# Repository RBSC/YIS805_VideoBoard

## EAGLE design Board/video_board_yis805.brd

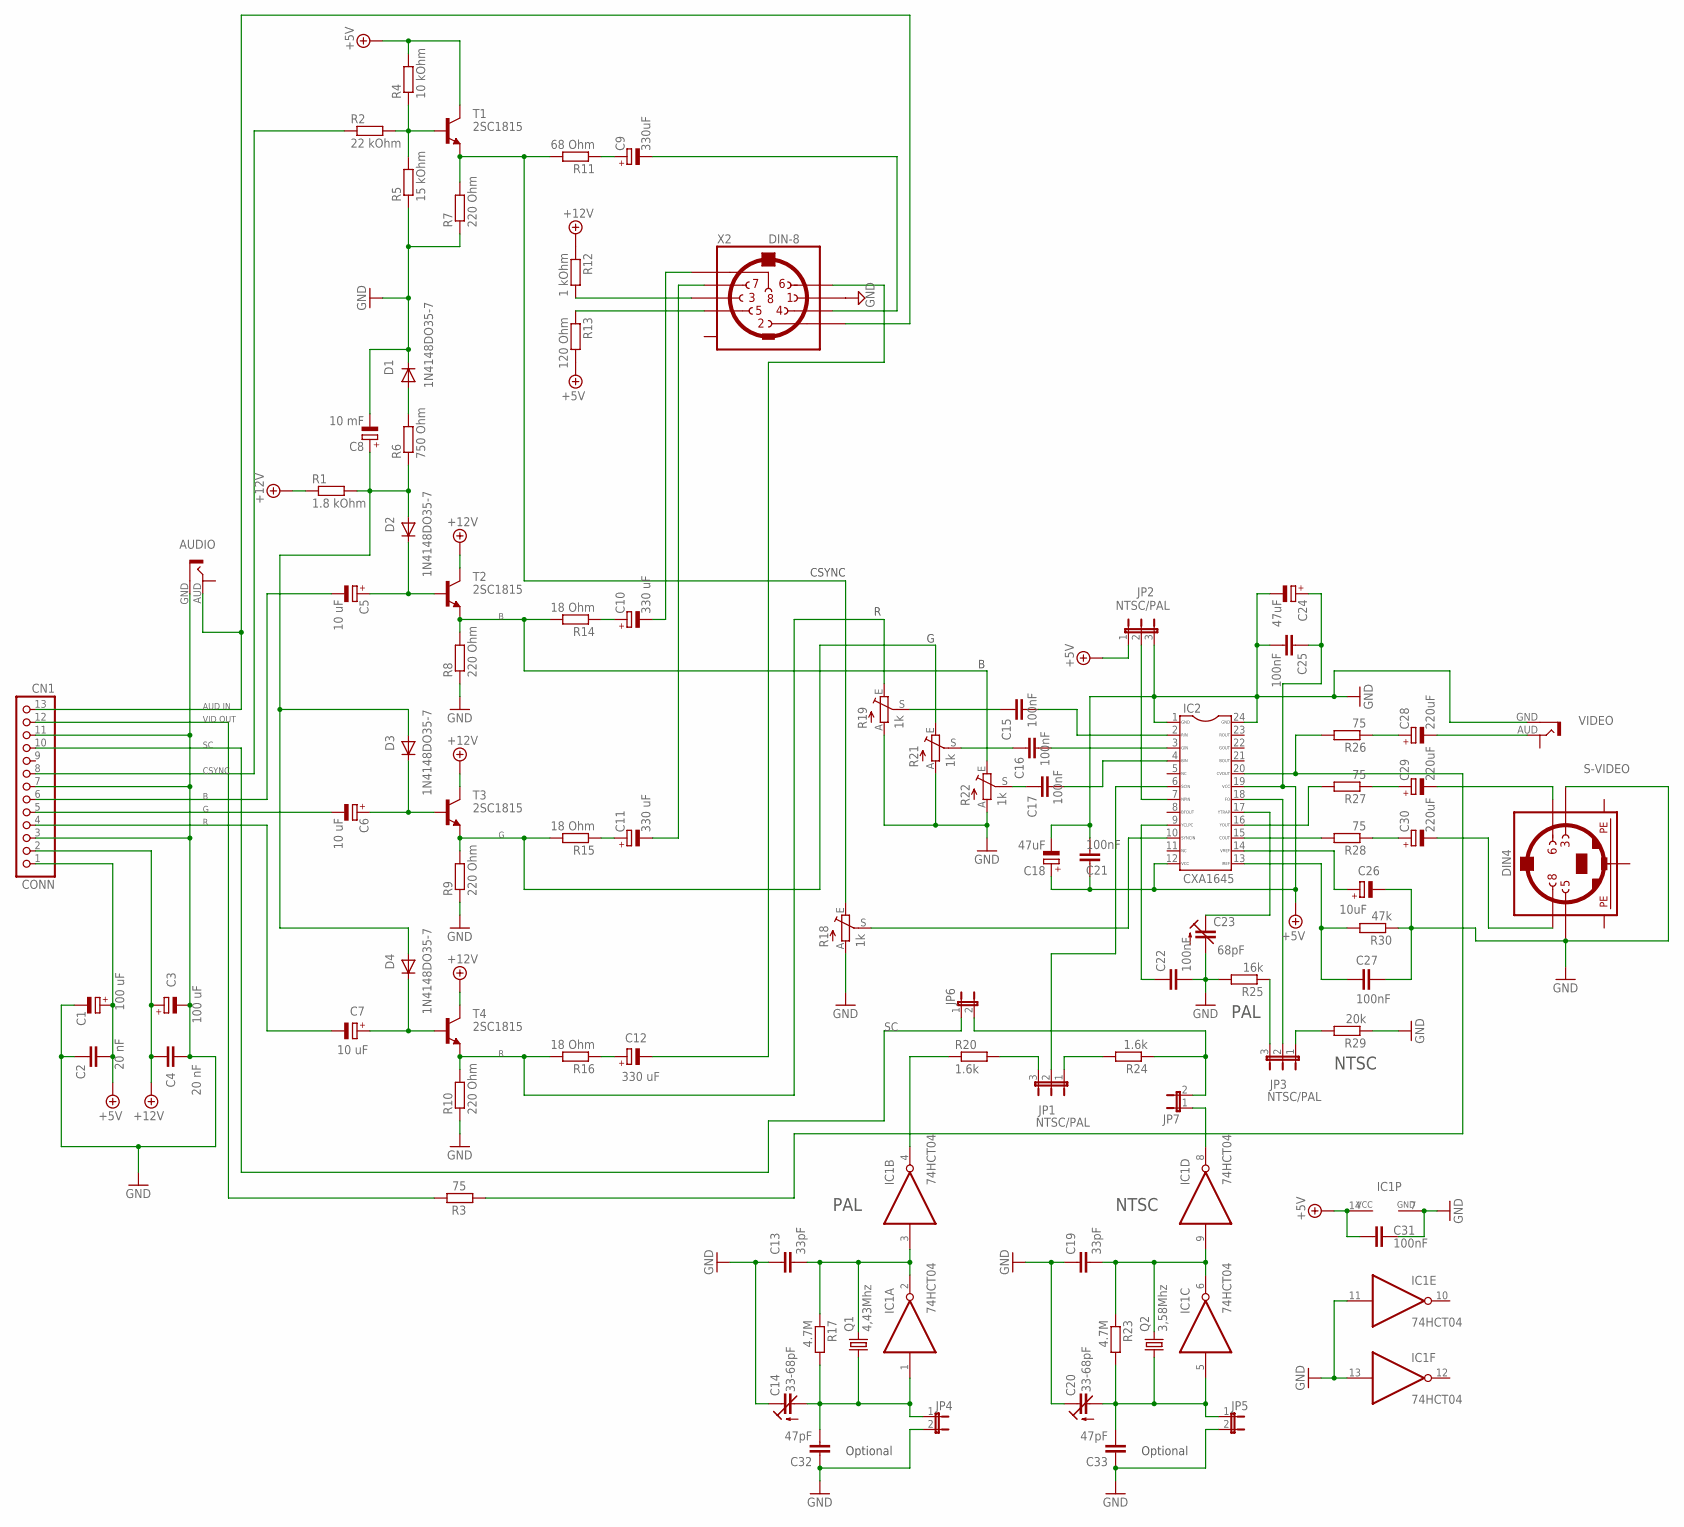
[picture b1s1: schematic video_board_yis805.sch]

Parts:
AUDIO: RCA
C1, C3: 100 uF; SMC_D
C2, C4: 20 nF; C0805
C5, C6, C7: 10 uF; SMC_B
C8: 10 mF; SMC_B
C9: 330uF; SMC_D
C10, C11, C12: 330 uF; SMC_D
C13, C19: 33pF; C0805
C14, C20: 33-68pF; CTRIMTZ03
C15, C16, C17, C21, C22, C25, C27, C31: 100nF; C0805
C18, C24: 47uF; SMC_B
C23: 68pF; CTRIMTZ03
C26: 10uF; SMC_B
C28, C29, C30: 220uF; SMC_D
C32, C33: 47pF; C0805
CONN: CN1; 1X13
D1, D2, D3, D4: 1N4148DO35-7; MINIMELF
IC1: 74HCT04; SO14
IC2: CXA1645; SOP24
JP1, JP2, JP3: NTSC/PAL; JP2
JP4, JP5, JP6, JP7: JP1E; JP1
Q1: 4,43Mhz; HC49/S; MPN HC49SM-3.6864-30-50-60-16-ATF
Q2: 3,58Mhz; HC49/S; MPN HC49SM-3.6864-30-50-60-16-ATF
R1: 1.8 kOhm; R0805
R2: 22 kOhm; R0805
R3, R26, R27, R28: 75; R0805
R4: 10 kOhm; R0805
R5: 15 kOhm; R0805
R6: 750 Ohm; R0805
R7, R8, R9, R10: 220 Ohm; R0805
R11: 68 Ohm; R0805
R12: 1 kOhm; R0805
R13: 120 Ohm; R0805
R14, R15, R16: 18 Ohm; R0805
R17, R23: 4.7M; R0805
R18, R19, R21, R22: 1k; CA6V
R20, R24: 1.6k; R0805
R25: 16k; R0805
R29: 20k; R0805
R30: 47k; R0805
S-VIDEO: DIN4; M_DIN4
T1, T2, T3, T4: 2SC1815; TO92-ECB
VIDEO: RCA
X2: DIN-8; DIN8

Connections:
+5V: C1.+, C2.1, C18.+, C21.1, C24.+, C25.1, C31.2, CONN.1, IC1.14 (VCC), IC2.12, IC2.19, JP2.1, R4.2, R13.2, T1.C
+12V: C3.+, C4.1, CONN.2, R1.1, R12.1, T2.C, T3.C, T4.C
GND: AUDIO.GND (GND1), C1.-, C2.2, C3.-, C4.2, C8.-, C13.1, C14.1 (E), C18.-, C19.1, C20.1 (E), C21.2, C22.2, C23.2 (A), C24.-, C25.2, C26.-, C27.2, C31.1, C32.1, C33.1, CONN.3, CONN.7, CONN.11, D1.C, IC1.7 (GND), IC1.11 (I), IC1.13 (I), IC2.1, IC2.24, JP2.3, JP4.2, JP5.2, R5.1, R7.1, R8.1, R9.1, R10.1, R18.A, R19.A, R21.A, R22.A, R25.2, R29.1, R30.1, S-VIDEO.3, S-VIDEO.5, VIDEO.GND (GND1), X2.1
unnamed: R10.2, R16.2, R19.E, T4.E
unnamed: C20.2 (A), C33.2, IC1.5 (I), JP5.1, Q2.1, R23.2
unnamed: JP6.2, JP7.2, R24.1
unnamed: CONN.8, R2.1
unnamed: R8.2, R14.2, R22.E, T2.E
unnamed: C15.1, R19.S
unnamed: C16.1, R21.S
unnamed: IC1.4 (O), R20.1
unnamed: JP1.1, R24.2
unnamed: C19.2, IC1.6 (O), IC1.9 (I), Q2.2, R23.1
unnamed: JP1.3, R20.2
unnamed: C8.+, D2.A, D3.A, D4.A, R1.2, R6.1
unnamed: JP3.3, R25.1
unnamed: IC2.7, JP2.2
unnamed: JP3.1, R29.2
unnamed: IC2.16, R27.2
unnamed: IC1.8 (O), JP7.1
unnamed: CONN.12, R3.2
unnamed: C23.1 (E), IC2.17
unnamed: C12.-, X2.6
unnamed: C11.-, X2.7
unnamed: C6.+, D3.C, T3.B
unnamed: C10.-, X2.8
unnamed: D1.A, R6.2
unnamed: C6.-, CONN.5
unnamed: C5.-, CONN.6
unnamed: AUDIO.AUD, CONN.13, X2.2
unnamed: C12.+, R16.1
unnamed: R12.2, X2.3
unnamed: R9.2, R15.2, R21.E, T3.E
unnamed: R13.1, X2.5
unnamed: C7.+, D4.C, T4.B
unnamed: C7.-, CONN.4
unnamed: C5.+, D2.C, T2.B
unnamed: R2.2, R4.1, R5.2, T1.B
unnamed: R7.2, R11.2, R18.E, T1.E
unnamed: C11.+, R15.1
unnamed: C10.+, R14.1
unnamed: C9.+, R11.1
unnamed: C9.-, X2.4
unnamed: C17.1, R22.S
unnamed: C16.2, IC2.3
unnamed: C15.2, IC2.2
unnamed: C17.2, IC2.4
unnamed: C14.2 (A), C32.2, IC1.1 (I), JP4.1, Q1.1, R17.2
unnamed: C13.2, IC1.2 (O), IC1.3 (I), Q1.2, R17.1
unnamed: IC2.10, R18.S
unnamed: IC2.6, JP1.2
unnamed: IC2.20, R3.1, R26.2
unnamed: C22.1, IC2.9
unnamed: IC2.18, JP3.2
unnamed: IC2.15, R28.2
unnamed: C28.+, R26.1
unnamed: C29.+, R27.1
unnamed: C30.+, R28.1
unnamed: C26.+, IC2.14
unnamed: C27.1, IC2.13, R30.2
unnamed: C28.-, VIDEO.AUD
unnamed: C29.-, S-VIDEO.6
unnamed: C30.-, S-VIDEO.8
PE1: S-VIDEO.SH1 (PE1)
PE2: S-VIDEO.SH2 (PE2)
PE3: S-VIDEO.SH3 (PE3)
SC: CONN.10, JP6.1

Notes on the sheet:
CSYNC
AUD IN
VID OUT
PAL
NTSC
Optional

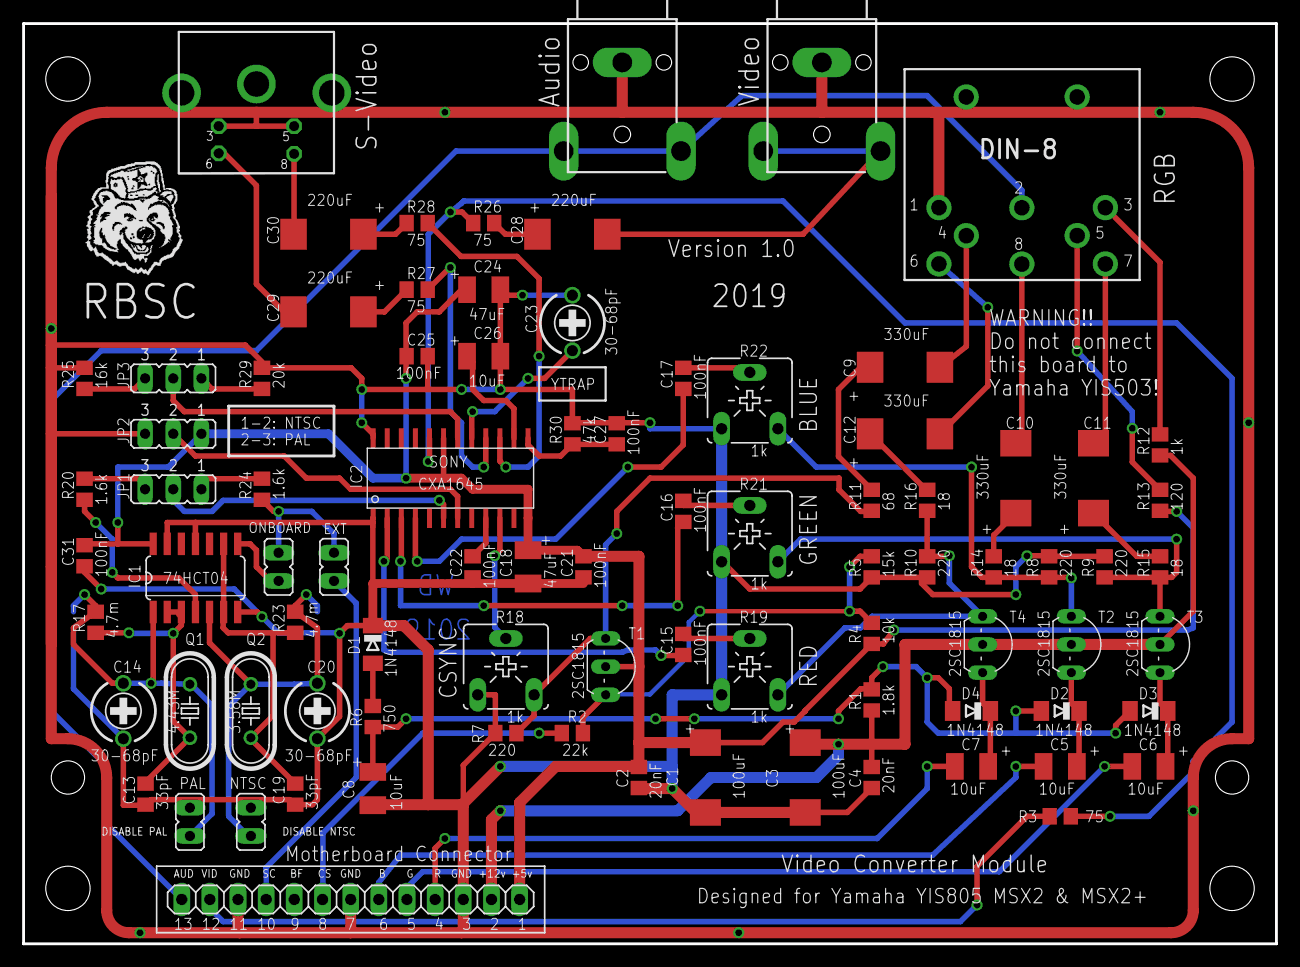
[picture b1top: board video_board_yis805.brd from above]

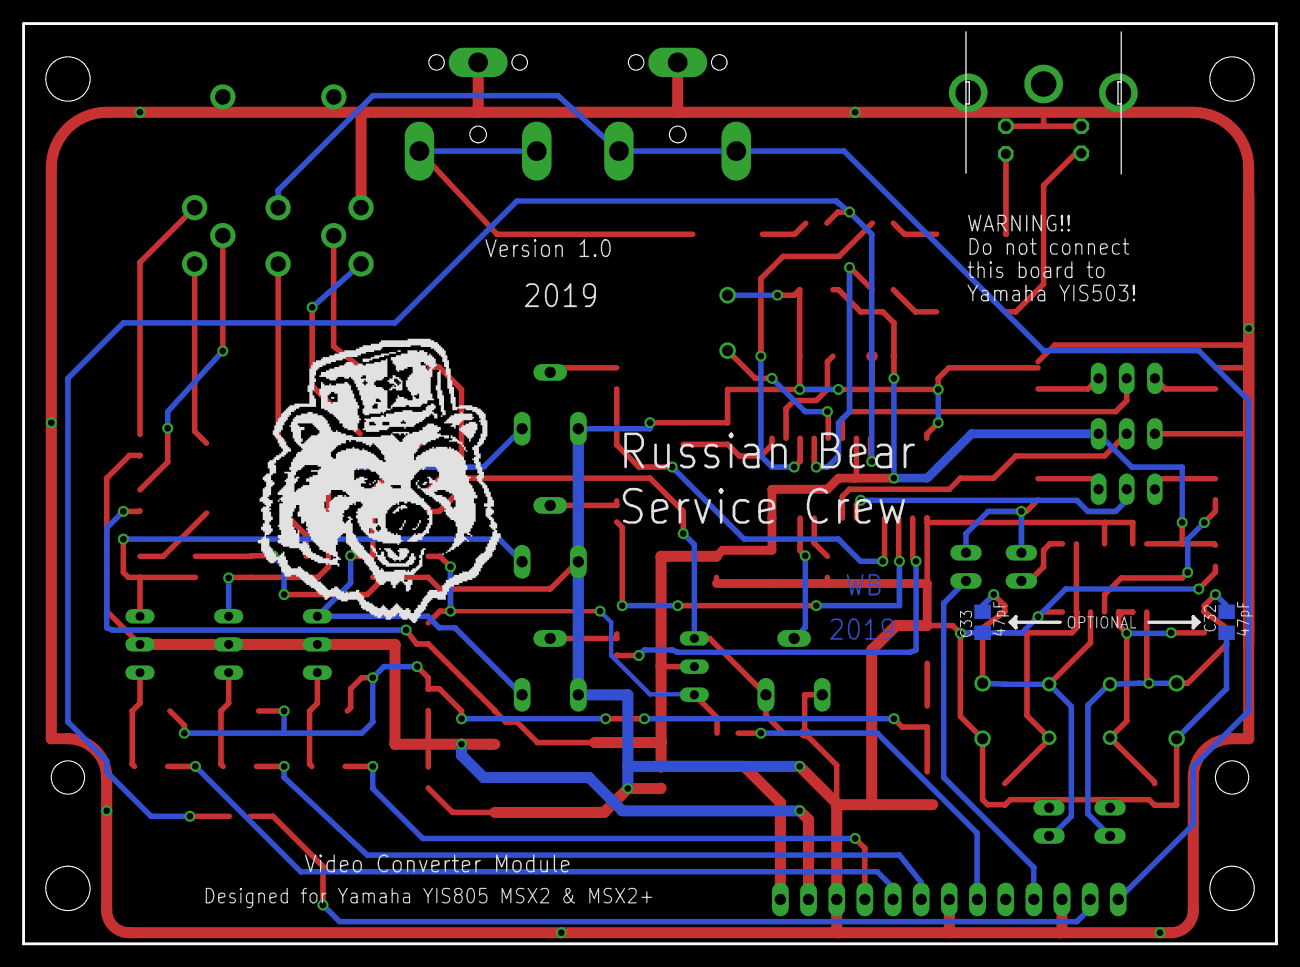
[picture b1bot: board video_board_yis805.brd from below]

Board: 2 copper layers, 113.0 x 83.0 mm, 87 parts (2 on the bottom side), 64 nets.

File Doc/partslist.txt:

Improved Video Board for Yamaha YIS805 MSX2/MSX2+ version 1.0
Copyright (c) 2019 RBSC

Partslist
---------

Part     Value          Device         Package   Library    Sheet

AUDIO    RCA            RCA            RCA       rca        1
C1       100 uF         CPOL-EUSMCD    SMC_D     rcl        1
C2       20 nF          C-EUC0805      C0805     rcl        1
C3       100 uF         CPOL-EUSMCD    SMC_D     rcl        1
C4       20 nF          C-EUC0805      C0805     rcl        1
C5       10 uF          CPOL-EUSMCB    SMC_B     rcl        1
C6       10 uF          CPOL-EUSMCB    SMC_B     rcl        1
C7       10 uF          CPOL-EUSMCB    SMC_B     rcl        1
C8       10 mF          CPOL-EUSMCB    SMC_B     rcl        1
C9       330uF          CPOL-EUSMCD    SMC_D     rcl        1
C10      330 uF         CPOL-EUSMCD    SMC_D     rcl        1
C11      330 uF         CPOL-EUSMCD    SMC_D     rcl        1
C12      330 uF         CPOL-EUSMCD    SMC_D     rcl        1
C13      33pF           C-EUC0805      C0805     rcl        1
C14      33-68pF        C-TRIMMTZ03    CTRIMTZ03 rcl        1
C15      100nF          C-EUC0805      C0805     rcl        1
C16      100nF          C-EUC0805      C0805     rcl        1
C17      100nF          C-EUC0805      C0805     rcl        1
C18      47uF           CPOL-EUSMCB    SMC_B     rcl        1
C19      33pF           C-EUC0805      C0805     rcl        1
C20      33-68pF        C-TRIMMTZ03    CTRIMTZ03 rcl        1
C21      100nF          C-EUC0805      C0805     rcl        1
C22      100nF          C-EUC0805      C0805     rcl        1
C23      68pF           C-TRIMMTZ03    CTRIMTZ03 rcl        1
C24      47uF           CPOL-EUSMCB    SMC_B     rcl        1
C25      100nF          C-EUC0805      C0805     rcl        1
C26      10uF           CPOL-EUSMCB    SMC_B     rcl        1
C27      100nF          C-EUC0805      C0805     rcl        1
C28      220uF          CPOL-EUSMCD    SMC_D     rcl        1
C29      220uF          CPOL-EUSMCD    SMC_D     rcl        1
C30      220uF          CPOL-EUSMCD    SMC_D     rcl        1
C31      100nF          C-EUC0805      C0805     rcl        1
C32      47pF           C-EUC0805      C0805     rcl        1
C33      47pF           C-EUC0805      C0805     rcl        1
CONN     CN1            PINHD-1X13     1X13      pinhead    1
D1       1N4148DO35-7   DIODE-MINIMELF MINIMELF  diode      1
D2       1N4148DO35-7   DIODE-MINIMELF MINIMELF  diode      1
D3       1N4148DO35-7   DIODE-MINIMELF MINIMELF  diode      1
D4       1N4148DO35-7   DIODE-MINIMELF MINIMELF  diode      1
IC1      74HCT04        74HCT04D       SO14      74xx-eu    1
IC2      CXA1645        CXA1645        SOP24     CXA1645M   1
JP1      NTSC/PAL       JP2E           JP2       jumper     1
JP2      NTSC/PAL       JP2E           JP2       jumper     1
JP3      NTSC/PAL       JP2E           JP2       jumper     1
Q1       4.433618 MHz   CRYSTALHC49S   HC49/S    crystal    1
Q2       3.579545 MHz   CRYSTALHC49S   HC49/S    crystal    1
R1       1.8 kOhm       R-EU_R0805     R0805     resistor   1
R2       22 kOhm        R-EU_R0805     R0805     resistor   1
R3       75             R-EU_R0805     R0805     rcl        1
R4       10 kOhm        R-EU_R0805     R0805     resistor   1
R5       15 kOhm        R-EU_R0805     R0805     resistor   1
R6       750 Ohm        R-EU_R0805     R0805     resistor   1
R7       220 Ohm        R-EU_R0805     R0805     resistor   1
R8       220 Ohm        R-EU_R0805     R0805     resistor   1
R9       220 Ohm        R-EU_R0805     R0805     resistor   1
R10      220 Ohm        R-EU_R0805     R0805     resistor   1
R11      68 Ohm         R-EU_R0805     R0805     resistor   1
R12      1 kOhm         R-EU_R0805     R0805     resistor   1
R13      120 Ohm        R-EU_R0805     R0805     resistor   1
R14      18 Ohm         R-EU_R0805     R0805     resistor   1
R15      18 Ohm         R-EU_R0805     R0805     resistor   1
R16      18 Ohm         R-EU_R0805     R0805     resistor   1
R17      4.7M           R-EU_R0805     R0805     rcl        1
R18      1k             TRIM_EU-CA6V   CA6V      pot        1
R19      1k             TRIM_EU-CA6V   CA6V      pot        1
R20      1.6k           R-EU_R0805     R0805     rcl        1
R21      1k             TRIM_EU-CA6V   CA6V      pot        1
R22      1k             TRIM_EU-CA6V   CA6V      pot        1
R23      4.7M           R-EU_R0805     R0805     rcl        1
R24      1.6k           R-EU_R0805     R0805     rcl        1
R25      16k            R-EU_R0805     R0805     rcl        1
R26      75             R-EU_R0805     R0805     rcl        1
R27      75             R-EU_R0805     R0805     rcl        1
R28      75             R-EU_R0805     R0805     rcl        1
R29      20k            R-EU_R0805     R0805     rcl        1
R30      47k            R-EU_R0805     R0805     rcl        1
S-VIDEO  DIN4           MINI_DIN_4     M_DIN4    mini_din   1
SJ1      CPU-CS         SJ             SJ        jumper     1
SJ2      GEN-CS         SJ             SJ        jumper     1
T1       2SC1815        2SC1815        TO92-ECB  transistor 1
T2       2SC1815        2SC1815        TO92-ECB  transistor 1
T3       2SC1815        2SC1815        TO92-ECB  transistor 1
T4       2SC1815        2SC1815        TO92-ECB  transistor 1
VIDEO    RCA            RCA            RCA       rca        1
X2       DIN-8          DIN-8          DIN8      din8       1

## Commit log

2019-12-11 :octocat: Added .gitattributes & .gitignore files
2019-12-11 Initial release 12.12.2019
    Initial release of the project's sources and docs
2019-12-21 Updated 21.12.2019
    Updated picture of the assembled board

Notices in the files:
Board/video_board_yis805.sch:
Copyright (c) 2019 by RBSC
